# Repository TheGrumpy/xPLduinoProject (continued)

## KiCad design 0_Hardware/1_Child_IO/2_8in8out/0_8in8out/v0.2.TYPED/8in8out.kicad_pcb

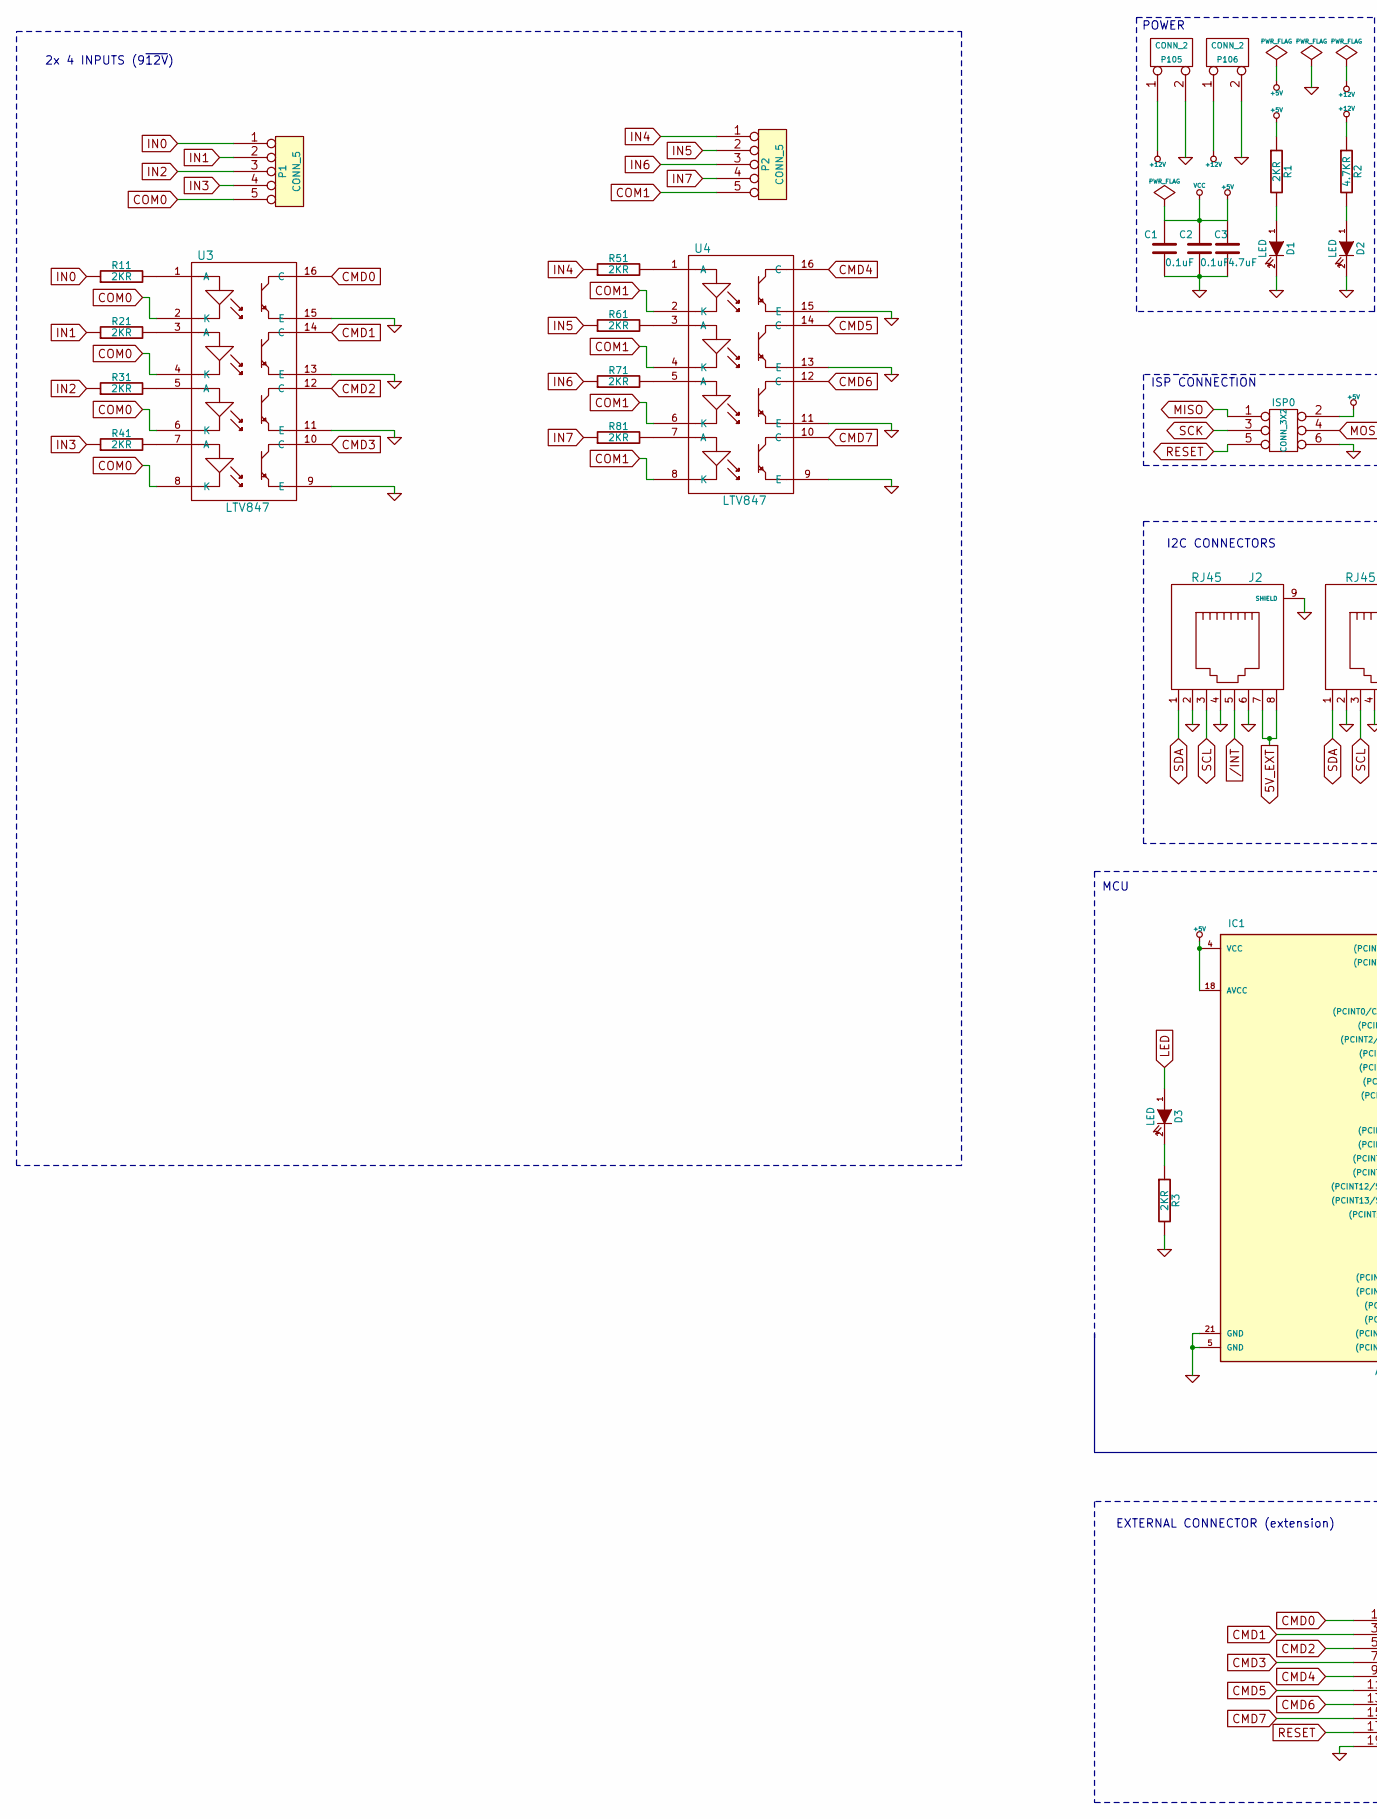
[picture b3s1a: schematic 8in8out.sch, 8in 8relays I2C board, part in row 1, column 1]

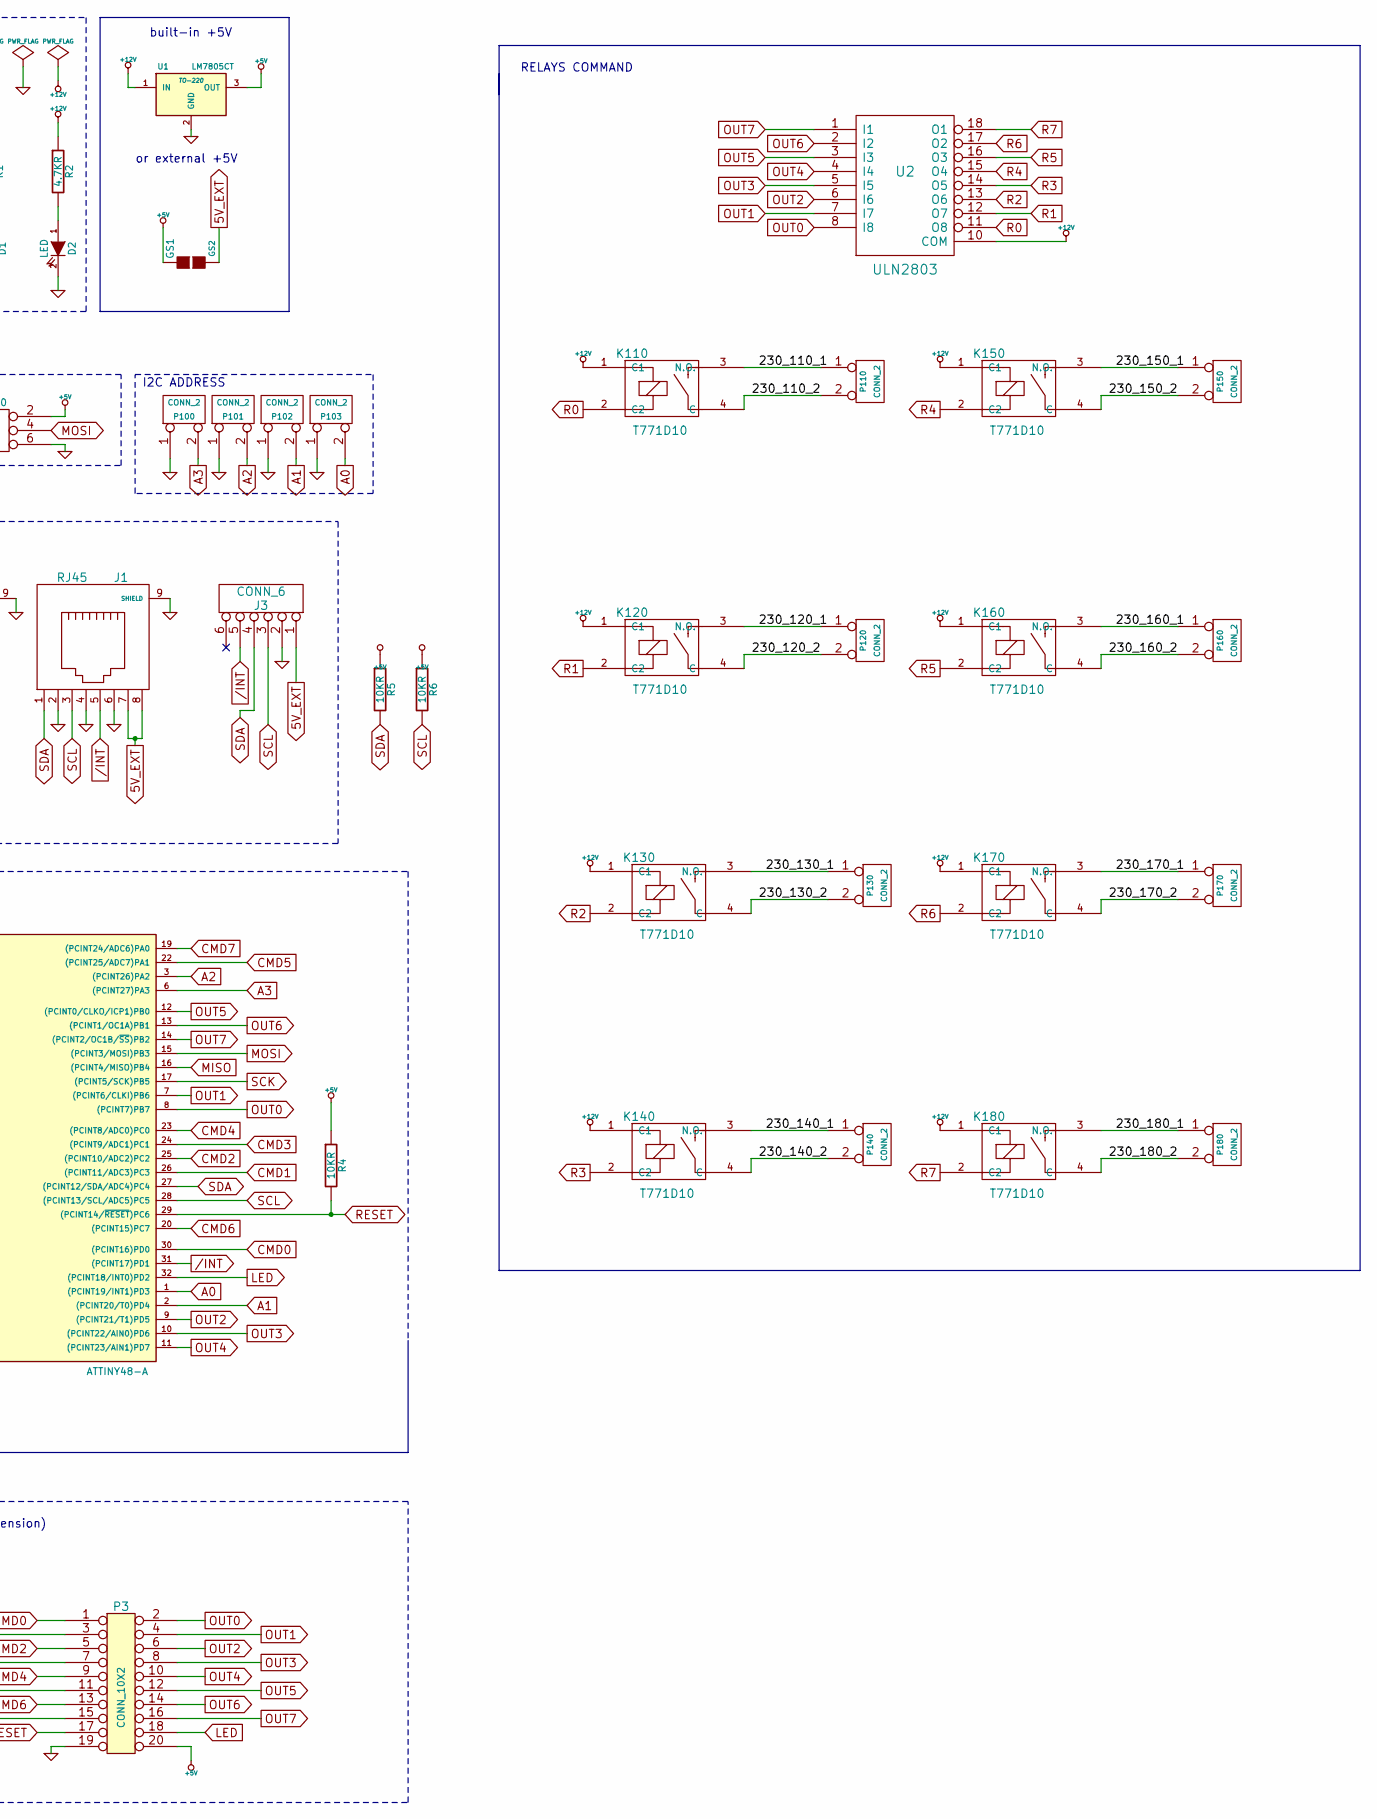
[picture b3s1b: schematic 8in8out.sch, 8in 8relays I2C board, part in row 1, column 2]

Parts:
C1, C2: 0.1uF
C3: 4.7uF
D1, D2, D3: LED
GS1: GS2
IC1: ATTINY48-A; TQFP32
ISP0: CONN_3X2
J1, J2: RJ45
J3: CONN_6
K110, K120, K130, K140, K150, K160, K170, K180: T771D10; G5T-1-12VDC
P1, P2: CONN_5
P3: CONN_10X2
P100, P101, P102, P103, P105, P106, P110, P120, P130, P140, P150, P160, P170, P180: CONN_2
R1, R3, R11, R21, R31, R41, R51, R61, R71, R81: 2KR
R2: 4.7KR
R4, R5, R6: 10KR
U1: LM7805CT; TO-220
U2: ULN2803
U3, U4: LTV847

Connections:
5V_EXT: GS1.2 (G2), J1.7, J1.8, J2.7, J2.8, J3.1
+5V: C1.1, C2.1, C3.1, GS1.1 (G1), IC1.4 (VCC), IC1.18 (AVCC), ISP0.2, P3.20, R1.1, R4.1, R5.1, R6.1, U1.3 (OUT)
+12V: K110.1 (C1), K120.1 (C1), K130.1 (C1), K140.1 (C1), K150.1 (C1), K160.1 (C1), K170.1 (C1), K180.1 (C1), P105.1, P106.1, R2.1, U1.1 (IN), U2.10 (COM)
/230_110_1: K110.3 (N.O.), P110.1
/230_110_2: K110.4 (C), P110.2 (PM)
/230_120_1: K120.3 (N.O.), P120.1
/230_120_2: K120.4 (C), P120.2 (PM)
/230_130_1: K130.3 (N.O.), P130.1
/230_130_2: K130.4 (C), P130.2 (PM)
/230_140_1: K140.3 (N.O.), P140.1
/230_140_2: K140.4 (C), P140.2 (PM)
/230_150_1: K150.3 (N.O.), P150.1
/230_150_2: K150.4 (C), P150.2 (PM)
/230_160_1: K160.3 (N.O.), P160.1
/230_160_2: K160.4 (C), P160.2 (PM)
/230_170_1: K170.3 (N.O.), P170.1
/230_170_2: K170.4 (C), P170.2 (PM)
/230_180_1: K180.3 (N.O.), P180.1
/230_180_2: K180.4 (C), P180.2 (PM)
/INT: IC1.31 ((PCINT17)PD1), J1.5, J2.5, J3.5
A0: IC1.1 ((PCINT19/INT1)PD3), P103.2 (PM)
A1: IC1.2 ((PCINT20/T0)PD4), P102.2 (PM)
A2: IC1.3 ((PCINT26)PA2), P101.2 (PM)
A3: IC1.6 ((PCINT27)PA3), P100.2 (PM)
CMD0: IC1.30 ((PCINT16)PD0), P3.1, U3.16 (C)
CMD1: IC1.26 ((PCINT11/ADC3)PC3), P3.3, U3.14 (C)
CMD2: IC1.25 ((PCINT10/ADC2)PC2), P3.5, U3.12 (C)
CMD3: IC1.24 ((PCINT9/ADC1)PC1), P3.7, U3.10 (C)
CMD4: IC1.23 ((PCINT8/ADC0)PC0), P3.9, U4.16 (C)
CMD5: IC1.22 ((PCINT25/ADC7)PA1), P3.11, U4.14 (C)
CMD6: IC1.20 ((PCINT15)PC7), P3.13, U4.12 (C)
CMD7: IC1.19 ((PCINT24/ADC6)PA0), P3.15, U4.10 (C)
COM0: P1.5, U3.2 (K), U3.4 (K), U3.6 (K), U3.8 (K)
COM1: P2.5, U4.2 (K), U4.4 (K), U4.6 (K), U4.8 (K)
GND: C1.2, C2.2, C3.2, D1.2 (K), D2.2 (K), IC1.5 (GND), IC1.21 (GND), ISP0.6, J1.2, J1.4, J1.6, J1.9 (SHIELD), J2.2, J2.4, J2.6, J2.9 (SHIELD), J3.2, P3.19, P100.1, P101.1, P102.1, P103.1, P105.2 (PM), P106.2 (PM), R3.2, U1.2 (GND), U2.9 (GND), U3.9 (E), U3.11 (E), U3.13 (E), U3.15 (E), U4.9 (E), U4.11 (E), U4.13 (E), U4.15 (E)
IN0: P1.1, R11.1
IN1: P1.2, R21.1
IN2: P1.3, R31.1
IN3: P1.4, R41.1
IN4: P2.1, R51.1
IN5: P2.2, R61.1
IN6: P2.3, R71.1
IN7: P2.4, R81.1
LED: D3.1 (A), IC1.32 ((PCINT18/INT0)PD2), P3.18
MISO: IC1.16 ((PCINT4/MISO)PB4), ISP0.1
MOSI: IC1.15 ((PCINT3/MOSI)PB3), ISP0.4
unnamed: R51.2, U4.1 (A)
unnamed: R61.2, U4.3 (A)
unnamed: R71.2, U4.5 (A)
unnamed: R81.2, U4.7 (A)
unnamed: R11.2, U3.1 (A)
unnamed: R21.2, U3.3 (A)
unnamed: R31.2, U3.5 (A)
unnamed: R41.2, U3.7 (A)
unnamed: D3.2 (K), R3.1
unnamed: D2.1 (A), R2.2
unnamed: D1.1 (A), R1.2
OUT0: IC1.8 ((PCINT7)PB7), P3.2, U2.8 (I8)
OUT1: IC1.7 ((PCINT6/CLKI)PB6), P3.4, U2.7 (I7)
OUT2: IC1.9 ((PCINT21/T1)PD5), P3.6, U2.6 (I6)
OUT3: IC1.10 ((PCINT22/AIN0)PD6), P3.8, U2.5 (I5)
OUT4: IC1.11 ((PCINT23/AIN1)PD7), P3.10, U2.4 (I4)
OUT5: IC1.12 ((PCINT0/CLKO/ICP1)PB0), P3.12, U2.3 (I3)
OUT6: IC1.13 ((PCINT1/OC1A)PB1), P3.14, U2.2 (I2)
OUT7: IC1.14 ((PCINT2/OC1B/~SS~)PB2), P3.16, U2.1 (I1)
R0: K110.2 (C2), U2.11 (O8)
R1: K120.2 (C2), U2.12 (O7)
R2: K130.2 (C2), U2.13 (O6)
R3: K140.2 (C2), U2.14 (O5)
R4: K150.2 (C2), U2.15 (O4)
R5: K160.2 (C2), U2.16 (O3)
R6: K170.2 (C2), U2.17 (O2)
R7: K180.2 (C2), U2.18 (O1)
RESET: IC1.29 ((PCINT14/~RESET~)PC6), ISP0.5, P3.17, R4.2
SCK: IC1.17 ((PCINT5/SCK)PB5), ISP0.3
SCL: IC1.28 ((PCINT13/SCL/ADC5)PC5), J1.3, J2.3, J3.3, R6.2
SDA: IC1.27 ((PCINT12/SDA/ADC4)PC4), J1.1, J2.1, J3.4, R5.2

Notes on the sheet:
ISP CONNECTION
I2C ADDRESS
POWER
I2C CONNECTORS
MCU
built-in +5V
or external +5V
RELAYS COMMAND
2x 4 INPUTS (9~12V)
EXTERNAL CONNECTOR (extension)

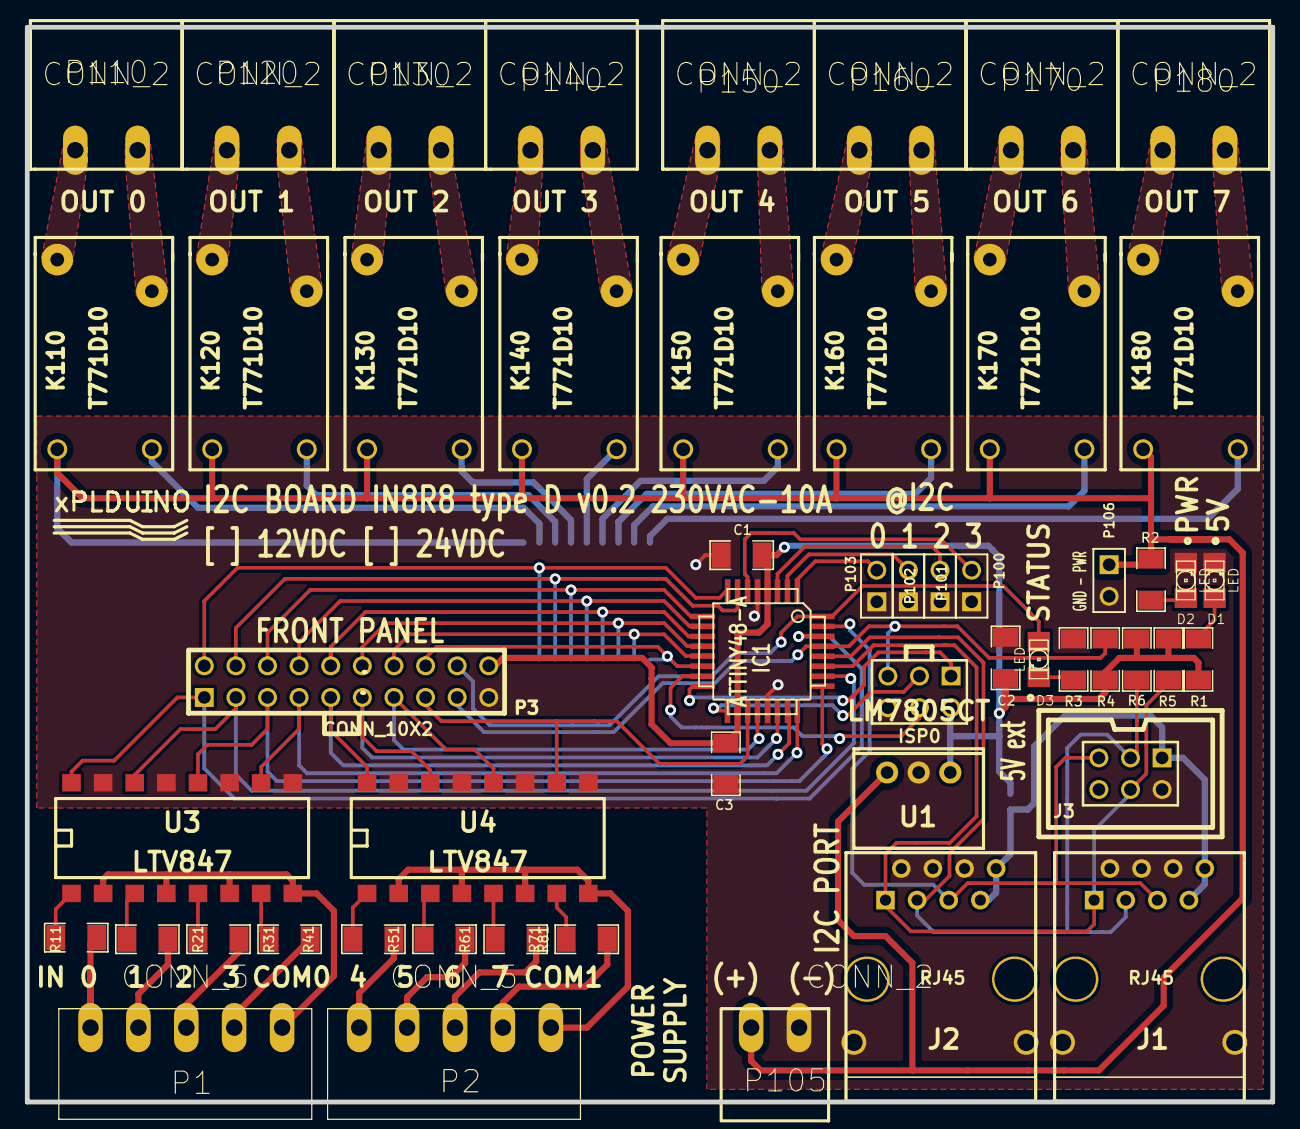
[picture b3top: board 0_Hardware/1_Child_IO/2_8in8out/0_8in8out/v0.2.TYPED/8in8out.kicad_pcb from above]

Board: 2 copper layers, 100.1 x 86.4 mm, 56 parts (0 on the bottom side), 77 nets.

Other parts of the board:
logo_xplduino: VAL**; logo_xplduino

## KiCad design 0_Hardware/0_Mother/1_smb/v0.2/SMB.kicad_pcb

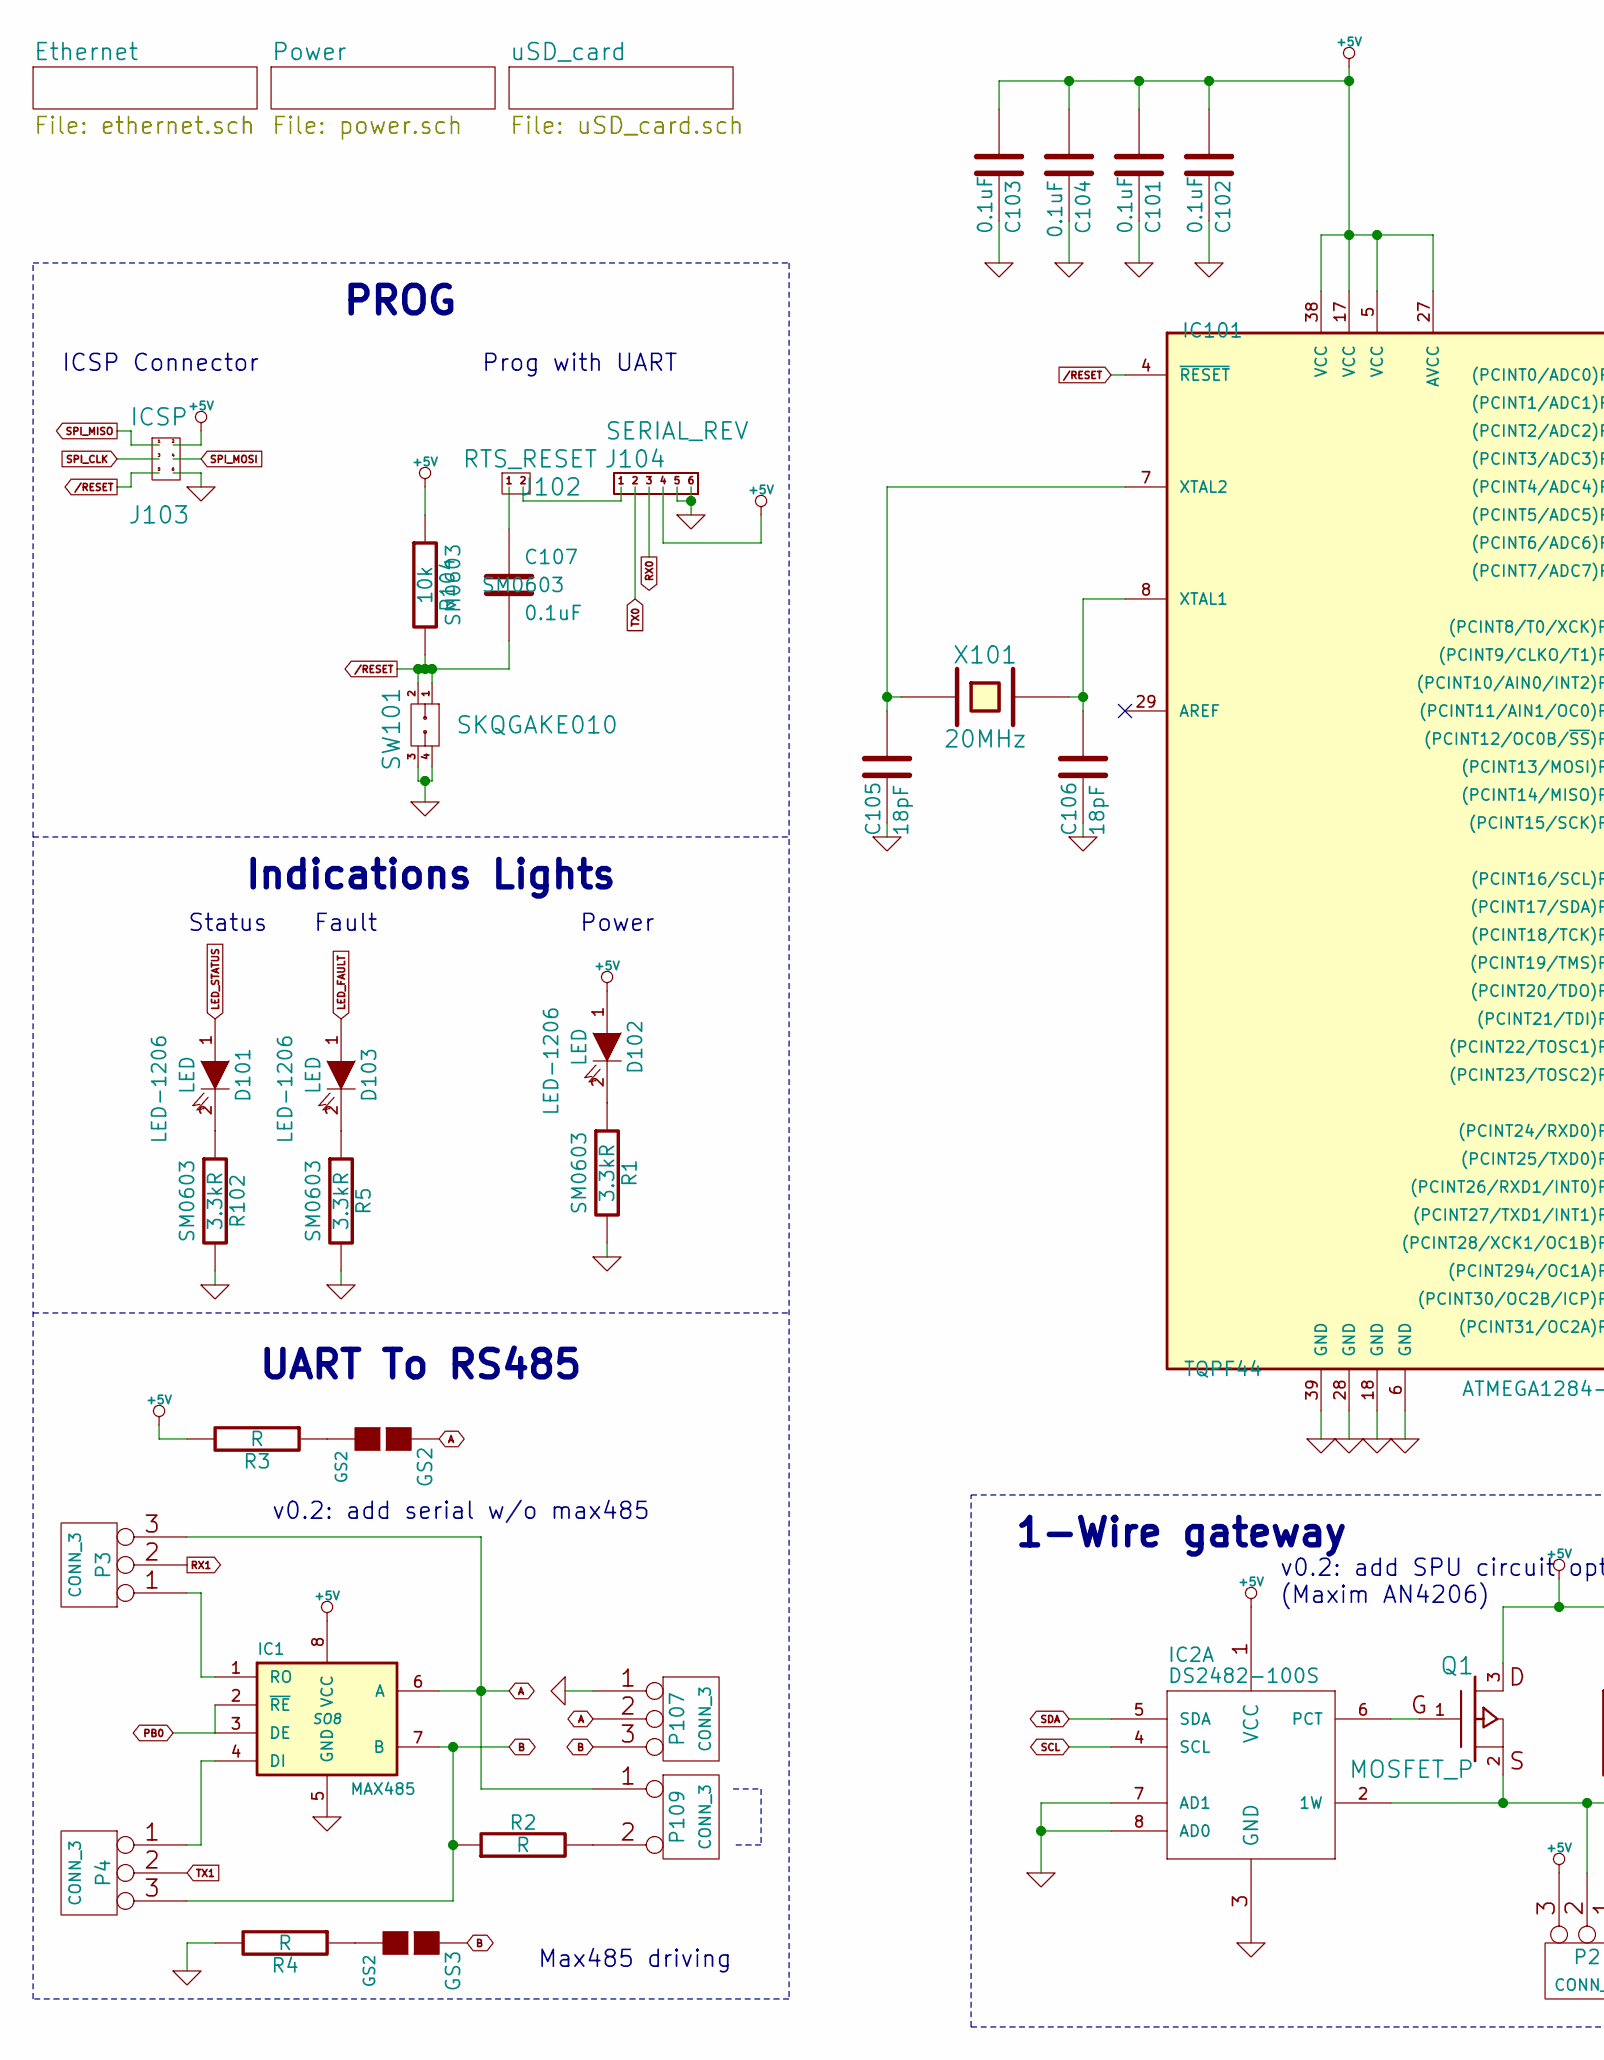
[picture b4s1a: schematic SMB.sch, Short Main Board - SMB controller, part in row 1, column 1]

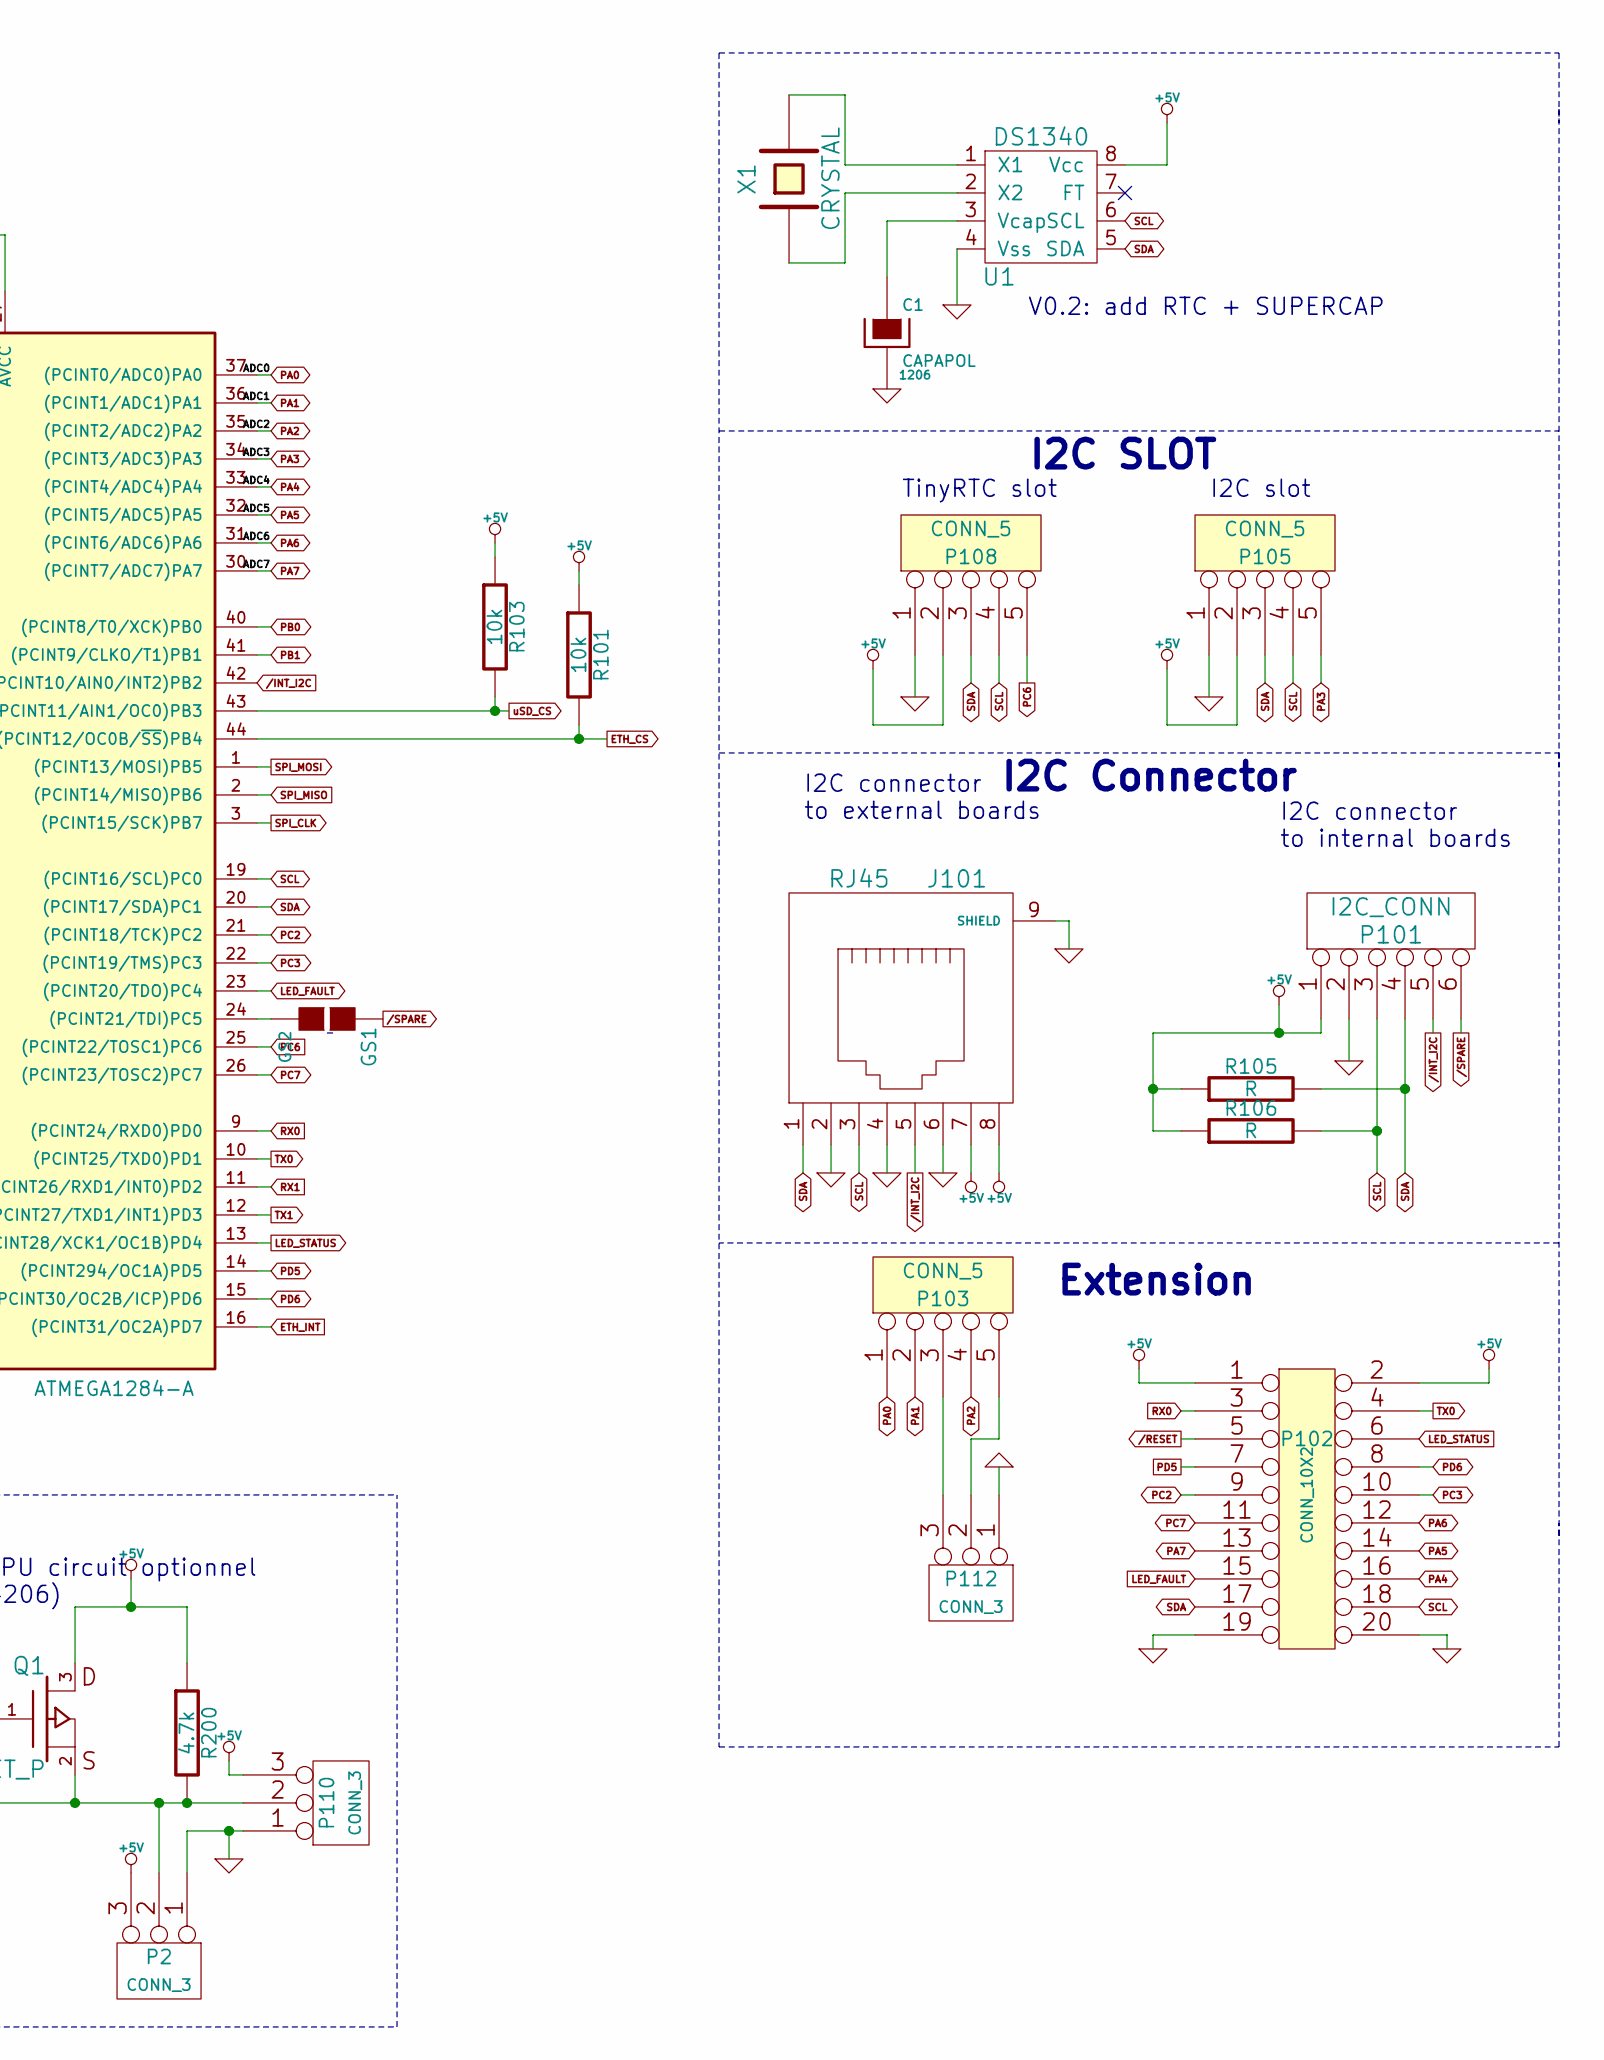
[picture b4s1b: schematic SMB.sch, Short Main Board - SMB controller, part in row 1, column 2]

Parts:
C1: CAPAPOL; 1206
C101, C102, C103, C104, C107: 0.1uF; SM0603
C105, C106: 18pF; SM0603
D101, D102, D103: LED; LED-1206
GS1, GS2, GS3: GS2
IC1: MAX485; SO8
IC2: DS2482-100S; 1wire-SO08
IC101: ATMEGA1284-A; TQPF44
J101: RJ45
J102: RTS_RESET
J103: ICSP
J104: SERIAL_REV
P2, P3, P4, P107, P109, P110, P112: CONN_3
P101: I2C_CONN
P102: CONN_10X2
P103, P105, P108: CONN_5
Q1: MOSFET_P
R1, R5, R102: 3.3kR; SM0603
R2, R3, R4, R105, R106: R
R101, R103, R104: 10k; SM0603
R200: 4.7k; SM0603
SW101: SKQGAKE010
U1: DS1340
X1: CRYSTAL
X101: 20MHz

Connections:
+5V: C101.1, C102.1, C103.1, C104.2, D102.1 (A), IC1.8 (VCC), IC2.1 (VCC), IC101.5 (VCC), IC101.17 (VCC), IC101.27 (AVCC), IC101.38 (VCC), J101.7, J101.8, J103.2, J104.4, P2.3, P101.1, P102.1, P102.2, P105.2, P108.2, P110.3, Q1.3, R3.2, R101.1, R103.1, R104.1, R105.1, R106.1, R200.1, U1.8 (Vcc); also elsewhere on the board
/INT_I2C: IC101.42 ((PCINT10/AIN0/INT2)PB2), J101.5, P101.5
/RESET: C107.2, IC101.4 (~RESET), J103.5, P102.5, R104.2, SW101.1, SW101.2; also elsewhere on the board
/SPARE: GS1.1 (G1), P101.6
A: GS2.1 (G1), IC1.6 (A), P3.3, P107.2 (PM), P109.1
B: GS3.1 (G1), IC1.7 (B), P4.3, P107.3, R2.1
ETH_CS: IC101.44 ((PCINT12/OC0B/~SS~)PB4), R101.2; also elsewhere on the board
ETH_INT: IC101.16 ((PCINT31/OC2A)PD7); also elsewhere on the board
GND: C1.2, C101.2, C102.2, C103.2, C104.1, C105.2, C106.2, IC1.5 (GND), IC2.3 (GND), IC2.7 (AD1), IC2.8 (AD0), IC101.6 (GND), IC101.18 (GND), IC101.28 (GND), IC101.39 (GND), J101.2, J101.4, J101.6, J101.9 (SHIELD), J103.6, J104.5, J104.6, P2.1, P101.2, P102.19, P102.20, P105.1, P107.1, P108.1, P110.1, P112.1, R1.2, R4.2, R5.2, R102.2, SW101.3, SW101.4, U1.4 (Vss); also elsewhere on the board
LED_FAULT: D103.1 (A), IC101.23 ((PCINT20/TDO)PC4), P102.15
LED_STATUS: D101.1 (A), IC101.13 ((PCINT28/XCK1/OC1B)PD4), P102.6
unnamed: C106.1, IC101.8 (XTAL1), X101.2
unnamed: J102.2, J104.1
unnamed: C107.1, J102.1
unnamed: IC2.2 (1W), P2.2 (PM), P110.2 (PM), Q1.2, R200.2
unnamed: P109.2 (PM), R2.2
unnamed: C105.1, IC101.7 (XTAL2), X101.1
unnamed: U1.1 (X1), X1.2
unnamed: C1.1, U1.3 (Vcap)
unnamed: U1.2 (X2), X1.1
unnamed: P103.5, P112.2 (PM)
unnamed: P103.3, P112.3
unnamed: IC1.1 (RO), P3.1
unnamed: IC1.4 (DI), P4.1
unnamed: IC2.6 (PCT), Q1.1
unnamed: GS1.2 (G2), IC101.24 ((PCINT21/TDI)PC5)
unnamed: D103.2 (K), R5.1
unnamed: D101.2 (K), R102.1
unnamed: GS3.2 (G2), R4.1
unnamed: GS2.2 (G2), R3.1
unnamed: D102.2 (K), R1.1
PA0: IC101.37 ((PCINT0/ADC0)PA0), P103.1
PA1: IC101.36 ((PCINT1/ADC1)PA1), P103.2
PA2: IC101.35 ((PCINT2/ADC2)PA2), P103.4
PA3: IC101.34 ((PCINT3/ADC3)PA3), P105.5
PA4: IC101.33 ((PCINT4/ADC4)PA4), P102.16
PA5: IC101.32 ((PCINT5/ADC5)PA5), P102.14
PA6: IC101.31 ((PCINT6/ADC6)PA6), P102.12
PA7: IC101.30 ((PCINT7/ADC7)PA7), P102.13
PB0: IC1.2 (~RE~), IC1.3 (DE), IC101.40 ((PCINT8/T0/XCK)PB0)
PC2: IC101.21 ((PCINT18/TCK)PC2), P102.9
PC3: IC101.22 ((PCINT19/TMS)PC3), P102.10
PC6: IC101.25 ((PCINT22/TOSC1)PC6), P108.5
PC7: IC101.26 ((PCINT23/TOSC2)PC7), P102.11
PD5: IC101.14 ((PCINT294/OC1A)PD5), P102.7
PD6: IC101.15 ((PCINT30/OC2B/ICP)PD6), P102.8
RX0: IC101.9 ((PCINT24/RXD0)PD0), J104.3, P102.3
RX1: IC101.11 ((PCINT26/RXD1/INT0)PD2), P3.2 (PM)
SCL: IC2.4 (SCL), IC101.19 ((PCINT16/SCL)PC0), J101.3, P101.3, P102.18, P105.4, P108.4, R106.2, U1.6 (SCL)
SDA: IC2.5 (SDA), IC101.20 ((PCINT17/SDA)PC1), J101.1, P101.4, P102.17, P105.3, P108.3, R105.2, U1.5 (SDA)
SPI_CLK: IC101.3 ((PCINT15/SCK)PB7), J103.3; also elsewhere on the board
SPI_MISO: IC101.2 ((PCINT14/MISO)PB6), J103.1; also elsewhere on the board
SPI_MOSI: IC101.1 ((PCINT13/MOSI)PB5), J103.4; also elsewhere on the board
TX0: IC101.10 ((PCINT25/TXD0)PD1), J104.2, P102.4
TX1: IC101.12 ((PCINT27/TXD1/INT1)PD3), P4.2 (PM)
uSD_CS: IC101.43 ((PCINT11/AIN1/OC0)PB3), R103.2; also elsewhere on the board

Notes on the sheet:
ICSP Connector
TinyRTC slot
I2C connector to external boards
I2C connector to internal boards
I2C slot
I2C SLOT
I2C Connector
Extension
Max485 driving
PROG
Prog with UART
Indications Lights
Status
Power
UART To RS485
1-Wire gateway
Fault
V0.2: add RTC + SUPERCAP
v0.2: add SPU circuit optionnel (Maxim AN4206)
v0.2: add serial w/o max485

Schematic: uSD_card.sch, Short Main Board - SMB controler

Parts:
C215: 0.1uF; SM0603
J202: USD_CONN; DM3CS-SF
U301, U303: 74HC08

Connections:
3.3V: C215.2, J202.4 (Vdd), U303.14 (VCC); also elsewhere on the board
+5V: U301.14 (VCC); also elsewhere on the board
CLK_33: J202.5 (CLK), U303.3; also elsewhere on the board
CS_33: J202.2 (CD/DAT3), U303.8
GND: C215.1, J202.6 (Vss), U301.7 (GND), U303.7 (GND); also elsewhere on the board
MISO_33: J202.7 (DAT0), U301.1, U301.2; also elsewhere on the board
MOSI_33: J202.3 (CMD), U303.6; also elsewhere on the board
SPI_CLK: U303.1, U303.2; also elsewhere on the board
SPI_MISO: U301.3; also elsewhere on the board
SPI_MOSI: U303.4, U303.5; also elsewhere on the board
uSD_CS: U303.9, U303.10; also elsewhere on the board

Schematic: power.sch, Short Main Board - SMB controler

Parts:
C211: 10nF; SM0603
C212, C214, C309: 100nF; SM0603
C213: 10uF; SM0805
C301, C303, C304, C310, C311: 1uF; SM0805
C302: 150pF; SM0603
C305, C306, C307, C308, C312: 4.7uF; SM0805
D301: B280-13-F
L301: SRF1260-150M
P1, P5, P301: CONN_2
R301: 17.4k; SM0603
R302: 100k; SM0603
R303: 200k; SM0603
R304: 158k; SM0603
R305: 40.2k; SM0603
R306: 210k; SM0603
U202: LM1117IMP-3.3
U302: MP2562DS; SO8E

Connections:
3.3V: C213.1, C214.1, P5.1, U202.2 (OUT), U202.4 (OUT); also elsewhere on the board
+5V: C211.1, C212.1, C305.1, C306.1, C307.1, C308.1, C312.1, L301.3, L301.4, R306.2, U202.3 (IN); also elsewhere on the board
+12V: C301.1, C303.1, C304.1, C310.1, C311.1, P1.1, P301.1, R302.1, U302.7 (Vin)
GND: C211.2, C212.2, C213.2, C214.2, C301.2, C303.2, C304.2, C305.2, C306.2, C307.2, C308.2, C310.2, C311.2, C312.2, D301.1 (A), P1.2 (PM), P5.2 (PM), P301.2 (PM), R301.2, R303.2, R304.2, R305.2, U202.1 (GND), U302.5 (GND); also elsewhere on the board
unnamed: R301.1, R302.2, U302.2 (EN)
unnamed: C302.2, R304.1
unnamed: R303.1, U302.6 (FREQ)
unnamed: C302.1, U302.3 (COMP)
unnamed: C309.1, U302.8 (BST)
unnamed: R305.1, R306.1, U302.4 (FB)
pre_5V: C309.2, D301.2 (K), L301.1, L301.2, U302.1 (SW)

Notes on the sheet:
LM/NCP1117 and not MCP1826 crap from Microchip.
Self a cabler en mode parallele !!!
3.3V Rail

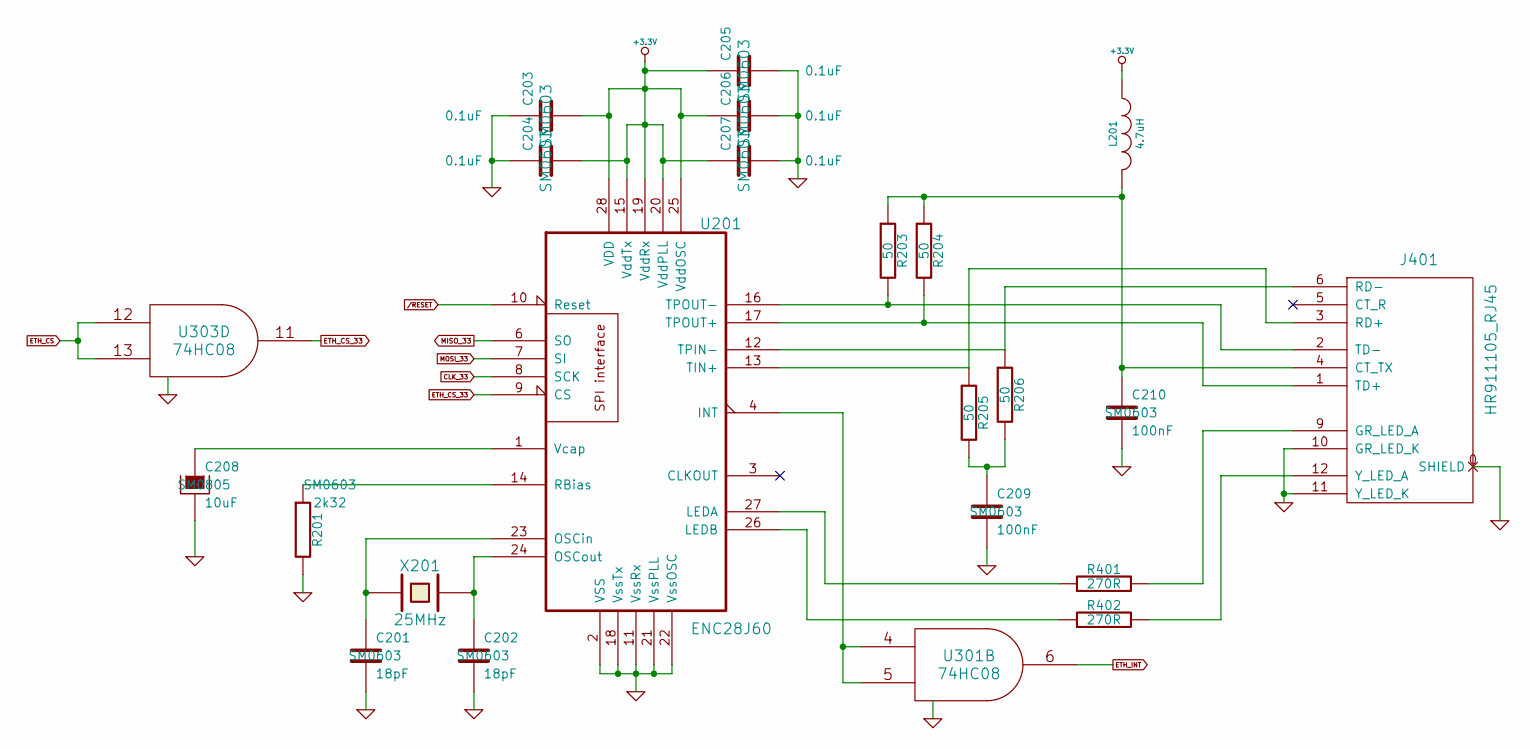
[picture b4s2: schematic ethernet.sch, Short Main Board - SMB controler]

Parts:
C201, C202: 18pF; SM0603
C203, C204, C205, C206, C207: 0.1uF; SM0603
C208: 10uF; SM0805
C209, C210: 100nF; SM0603
J401: HR911105_RJ45
L201: 4.7uH
R201: 2k32; SM0603
R203, R204, R205, R206: 50; SM0603
R401, R402: 270R
U201: ENC28J60
U301, U303: 74HC08
X201: 25MHz

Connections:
3.3V: C203.2, C204.2, C205.1, C206.1, C207.1, L201.1, U201.15 (VddTx), U201.19 (VddRx), U201.20 (VddPLL), U201.25 (VddOSC), U201.28 (VDD), U303.14 (VCC); also elsewhere on the board
+5V: U301.14 (VCC); also elsewhere on the board
/RESET: U201.10 (Reset); also elsewhere on the board
CLK_33: U201.8 (SCK); also elsewhere on the board
ETH_CS: U303.12, U303.13; also elsewhere on the board
ETH_CS_33: U201.9 (CS), U303.11
ETH_INT: U301.6; also elsewhere on the board
GND: C201.2, C202.2, C203.1, C204.1, C205.2, C206.2, C207.2, C208.2, C209.2, C210.2, J401.0 (SHIELD), J401.10 (GR_LED_K), J401.11 (Y_LED_K), R201.2, U201.2 (VSS), U201.11 (VssRx), U201.18 (VssTx), U201.21 (VssPLL), U201.22 (VssOSC), U301.7 (GND), U303.7 (GND); also elsewhere on the board
MISO_33: U201.6 (SO); also elsewhere on the board
MOSI_33: U201.7 (SI); also elsewhere on the board
unnamed: C208.1, U201.1 (Vcap)
unnamed: J401.6 (RD-), R206.1, U201.12 (TPIN-)
unnamed: R402.1, U201.26 (LEDB)
unnamed: J401.12 (Y_LED_A), R402.2
unnamed: C210.1, J401.4 (CT_TX), L201.2, R203.1, R204.1
unnamed: J401.1 (TD+), R204.2, U201.17 (TPOUT+)
unnamed: J401.3 (RD+), R205.1, U201.13 (TIN+)
unnamed: C209.1, R205.2, R206.2
unnamed: R401.1, U201.27 (LEDA)
unnamed: J401.9 (GR_LED_A), R401.2
unnamed: J401.2 (TD-), R203.2, U201.16 (TPOUT-)
unnamed: U201.4 (INT), U301.4, U301.5
unnamed: R201.1, U201.14 (RBias)
unnamed: C202.1, U201.24 (OSCout), X201.2
unnamed: C201.1, U201.23 (OSCin), X201.1
